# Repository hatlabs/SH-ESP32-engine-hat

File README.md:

# Engine Top Hat for SH-ESP32

This repository contains the hardware design files for the Engine Top Hat for SH-ESP32 (Engine Hat for short).

Engine Hat is a add-on circuit board that provides useful circuitry for connecting tachometers (RPM sensors), tank level sensors and engine alarms to an [SH-ESP32](https://hatlabs.github.io/sh-esp32).

The SH-ESP32 Engine Hat will be eventually available for purchase at [hatlabs.fi](https://hatlabs.fi).

Top view:

Bottom view:

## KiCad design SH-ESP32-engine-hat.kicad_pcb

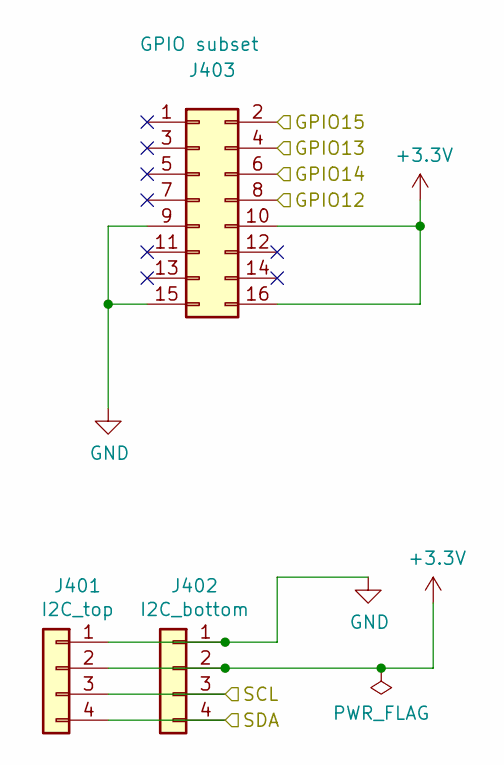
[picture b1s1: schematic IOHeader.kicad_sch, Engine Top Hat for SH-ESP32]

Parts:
J401: I2C_top; PinSocket_1x04_P2.54mm_Vertical; LCSC C225501
J402: I2C_bottom; PinHeader_1x04_P2.54mm_Vertical; LCSC C492403
J403: GPIO subset; PinSocket_2x08_P2.54mm_Vertical; LCSC C30734

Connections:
/Analog input/SCL: J401.3, J402.3; also elsewhere on the board
/Analog input/SDA: J401.4, J402.4; also elsewhere on the board
/DI1: J403.2; also elsewhere on the board
/DI2: J403.4; also elsewhere on the board
/DI3: J403.6; also elsewhere on the board
/DI4: J403.8; also elsewhere on the board
GND: J401.1, J402.1, J403.9, J403.15; also elsewhere on the board

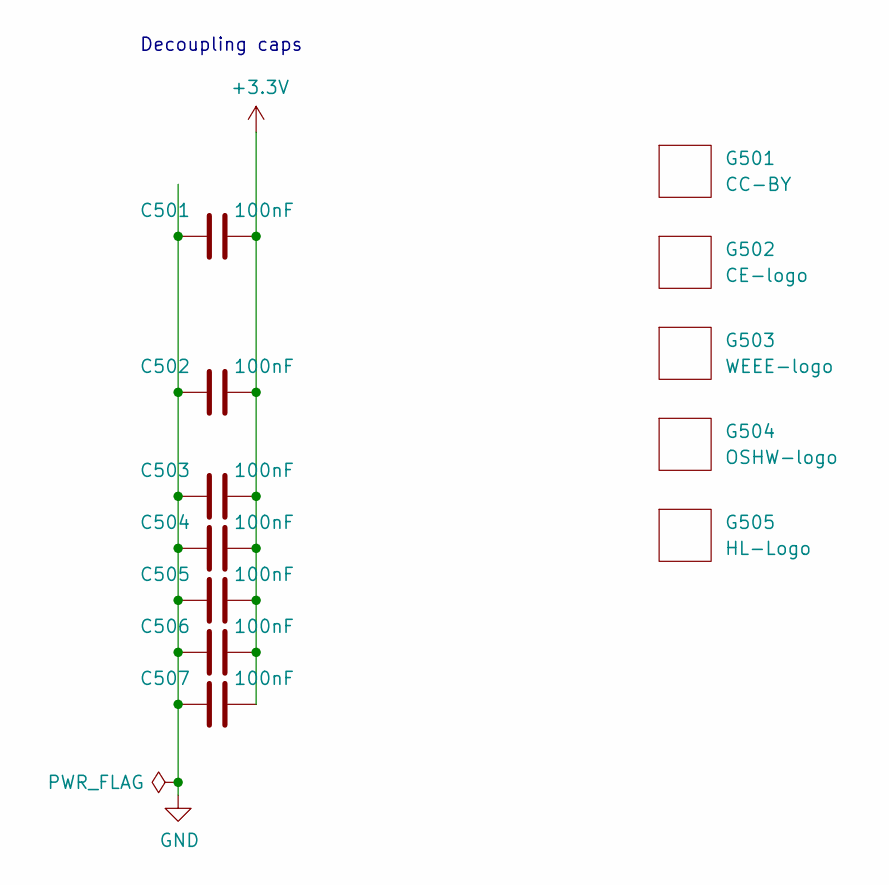
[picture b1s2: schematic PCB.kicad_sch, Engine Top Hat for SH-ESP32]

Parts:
C501, C502, C503, C504, C505, C506, C507: 100nF; C_0402_1005Metric; LCSC C1525
G501: CC-BY; cc-by_5mm
G502: CE-logo; CE-Logo_11.2x8mm_SilkScreen
G503: WEEE-logo; WEEE-Logo_5.6x8mm_SilkScreen
G504: OSHW-logo; OSHW-Logo2_9.8x8mm_SilkScreen
G505: HL-Logo; Hat_Labs_20mm

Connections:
GND: C501.1, C502.1, C503.1, C504.1, C505.1, C506.1, C507.1; also elsewhere on the board

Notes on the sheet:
Decoupling caps

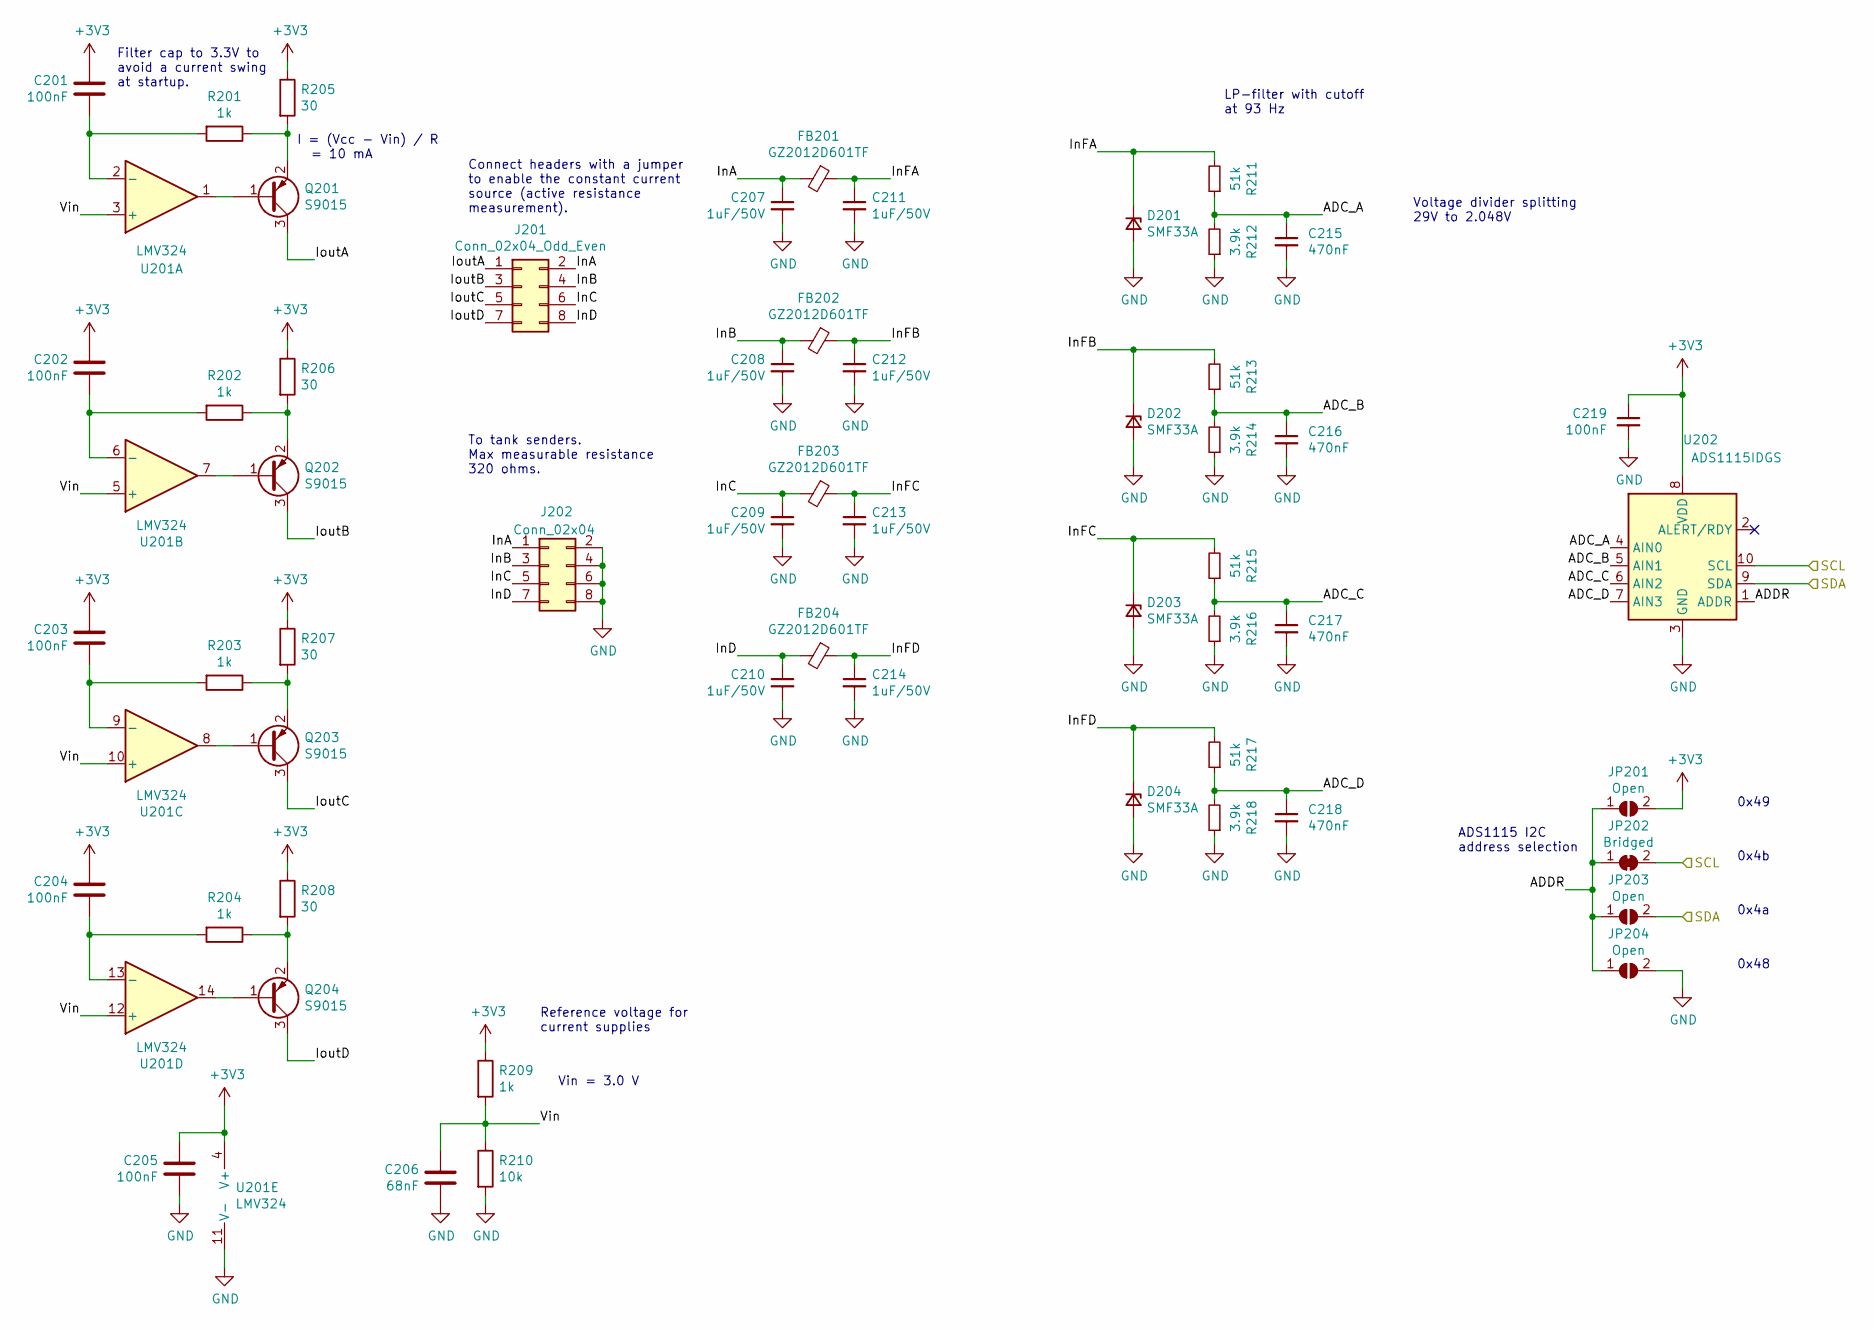
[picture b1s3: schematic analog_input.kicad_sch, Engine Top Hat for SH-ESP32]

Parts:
C201, C202, C203, C204, C205, C219: 100nF; C_0402_1005Metric; LCSC C1525
C206: 68nF; C_0603_1608Metric; LCSC C31658
C207, C208, C209, C210, C211, C212, C213, C214: 1uF/50V; C_0603_1608Metric; LCSC C15849
C215, C216, C217, C218: 470nF; C_0402_1005Metric; LCSC C47339
D201, D202, D203, D204: SMF33A; D_SOD-123F; LCSC C523840
FB201, FB202, FB203, FB204: GZ2012D601TF; L_0805_2012Metric; LCSC C1017
J201: Conn_02x04_Odd_Even; PinHeader_2x04_P2.54mm_Vertical; LCSC C124386
J202: Conn_02x04; PinHeader_2x04_P2.54mm_Horizontal; LCSC C358706
JP201, JP203, JP204: Open; SolderJumper-2_P1.3mm_Open_Pad1.0x1.5mm
JP202: Bridged; SolderJumper-2_P1.3mm_Bridged2Bar_RoundedPad1.0x1.5mm
Q201, Q202, Q203, Q204: S9015; SOT-323_SC-70; LCSC C106811
R201, R202, R203, R204, R209: 1k; R_0402_1005Metric; LCSC C11702
R205, R206, R207, R208: 30; R_0603_1608Metric; LCSC C22985
R210: 10k; R_0402_1005Metric; LCSC C25744
R211, R213, R215, R217: 51k; R_0402_1005Metric; LCSC C25794
R212, R214, R216, R218: 3.9k; R_0402_1005Metric; LCSC C51721
U201: LMV324; SOIC-14_3.9x8.7mm_P1.27mm; LCSC C362275
U202: ADS1115IDGS; TSSOP-10_3x3mm_P0.5mm; LCSC C37593

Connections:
/Analog input/ADC_A: C215.1, R211.1, R212.2, U202.4 (AIN0)
/Analog input/ADC_B: C216.1, R213.1, R214.2, U202.5 (AIN1)
/Analog input/ADC_C: C217.1, R215.1, R216.2, U202.6 (AIN2)
/Analog input/ADC_D: C218.1, R217.1, R218.2, U202.7 (AIN3)
/Analog input/ADDR: JP201.1 (A), JP202.1 (A), JP203.1 (A), JP204.1 (A), U202.1 (ADDR)
/Analog input/InA: C207.1, FB201.2, J201.2, J202.1
/Analog input/InB: C208.1, FB202.2, J201.4, J202.3
/Analog input/InC: C209.1, FB203.2, J201.6, J202.5
/Analog input/InD: C210.1, FB204.2, J201.8, J202.7
/Analog input/InFA: C211.1, D201.1 (K), FB201.1, R211.2
/Analog input/InFB: C212.1, D202.1 (K), FB202.1, R213.2
/Analog input/InFC: C213.1, D203.1 (K), FB203.1, R215.2
/Analog input/InFD: C214.1, D204.1 (K), FB204.1, R217.2
/Analog input/IoutA: J201.1, Q201.3 (C)
/Analog input/IoutB: J201.3, Q202.3 (C)
/Analog input/IoutC: J201.5, Q203.3 (C)
/Analog input/IoutD: J201.7, Q204.3 (C)
/Analog input/SCL: JP202.2 (B), U202.10 (SCL); also elsewhere on the board
/Analog input/SDA: JP203.2 (B), U202.9 (SDA); also elsewhere on the board
/Analog input/Vin: C206.1, R209.2, R210.1, U201.3 (+), U201.5 (+), U201.10 (+), U201.12 (+)
GND: C205.2, C206.2, C207.2, C208.2, C209.2, C210.2, C211.2, C212.2, C213.2, C214.2, C215.2, C216.2, C217.2, C218.2, C219.2, D201.2 (A), D202.2 (A), D203.2 (A), D204.2 (A), J202.2, J202.4, J202.6, J202.8, JP204.2 (B), R210.2, R212.1, R214.1, R216.1, R218.1, U201.11 (V-), U202.3 (GND); also elsewhere on the board
unnamed: C201.1, R201.2, U201.2 (-)
unnamed: C202.1, R202.2, U201.6 (-)
unnamed: C203.1, R203.2, U201.9 (-)
unnamed: C204.1, R204.2, U201.13 (-)
unnamed: Q201.1 (B), U201.1
unnamed: Q201.2 (E), R201.1, R205.2
unnamed: Q202.1 (B), U201.7
unnamed: Q202.2 (E), R202.1, R206.2
unnamed: Q203.1 (B), U201.8
unnamed: Q203.2 (E), R203.1, R207.2
unnamed: Q204.1 (B), U201.14
unnamed: Q204.2 (E), R204.1, R208.2

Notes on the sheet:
Vin = 3.0 V
ADS1115 I2C address selection
0x49
I = (Vcc - Vin) / R = 10 mA
Voltage divider splitting 29V to 2.048V
0x48
To tank senders. Max measurable resistance 320 ohms.
0x4a
Reference voltage for current supplies
0x4b
LP-filter with cutoff at 93 Hz
Connect headers with a jumper to enable the constant current source (active resistance measurement).
Filter cap to 3.3V to avoid a current swing at startup.

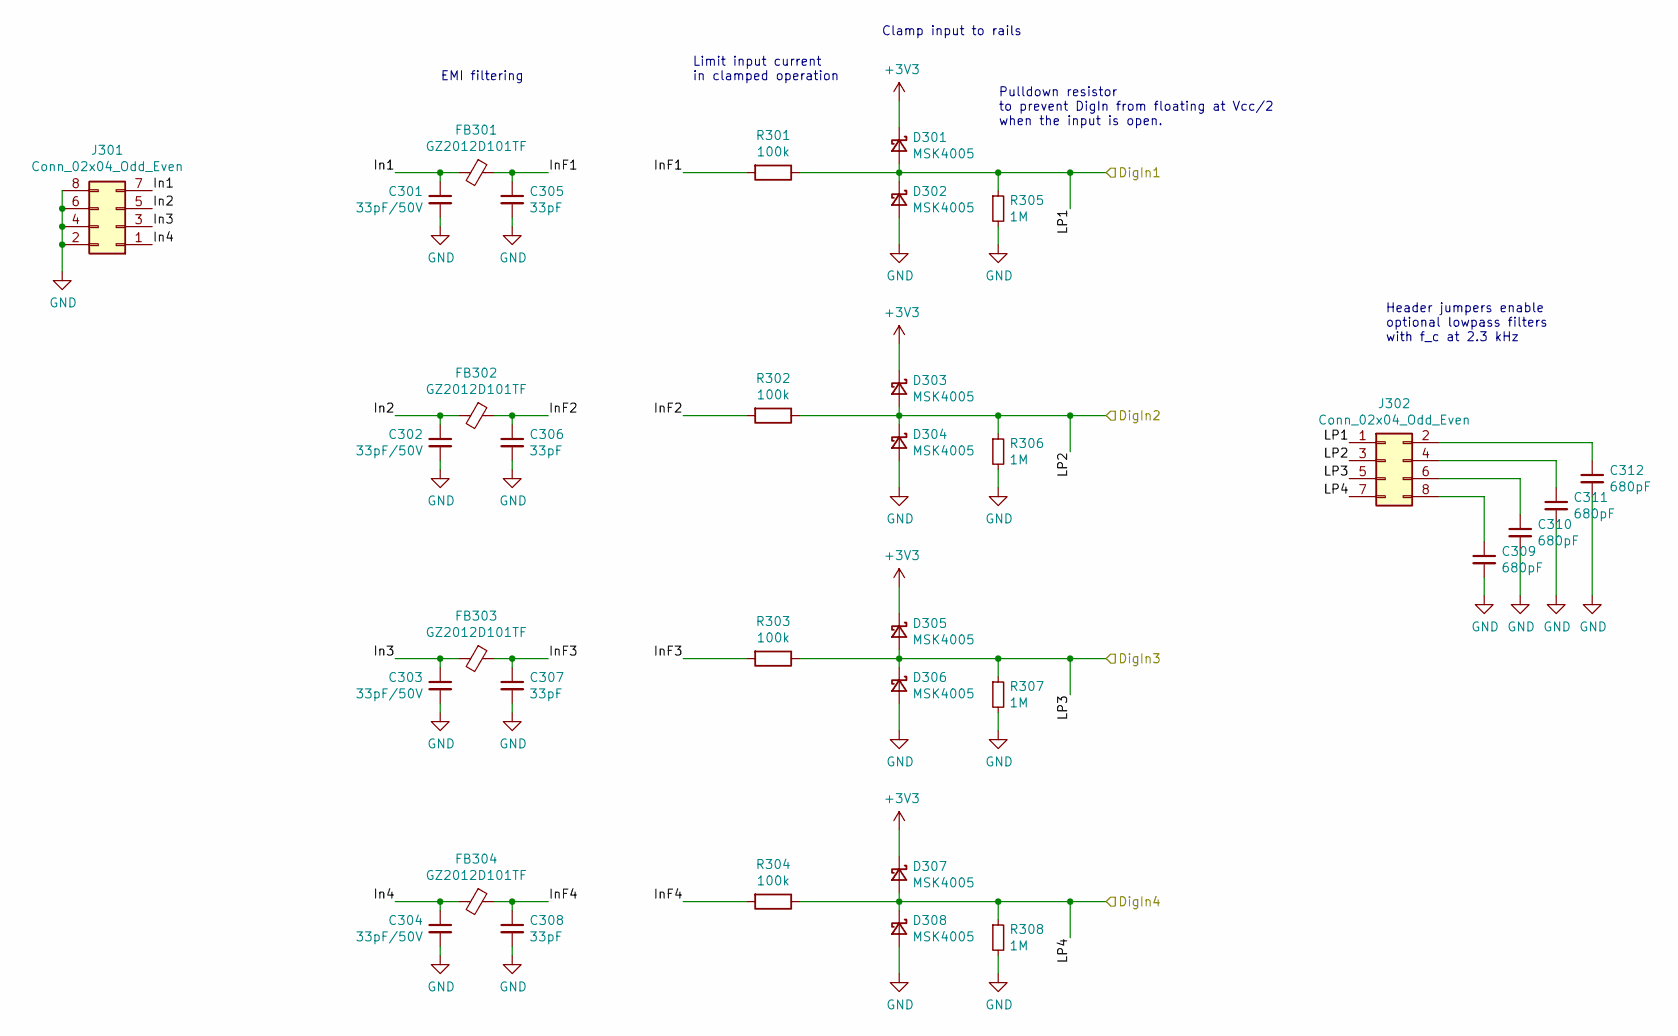
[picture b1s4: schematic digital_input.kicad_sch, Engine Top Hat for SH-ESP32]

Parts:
C301, C302, C303, C304: 33pF/50V; C_0603_1608Metric; LCSC C1663
C305, C306, C307, C308: 33pF; C_0402_1005Metric; LCSC C1562
C309, C310, C311, C312: 680pF; C_0603_1608Metric; LCSC C1630
D301, D302, D303, D304, D305, D306, D307, D308: MSK4005; D_SOD-523; LCSC C345957
FB301, FB302, FB303, FB304: GZ2012D101TF; L_0805_2012Metric; LCSC C1015
J301: Conn_02x04_Odd_Even; PinHeader_2x04_P2.54mm_Horizontal; LCSC C358706
J302: Conn_02x04_Odd_Even; PinHeader_2x04_P2.54mm_Vertical; LCSC C124386
R301, R302, R303, R304: 100k; R_0402_1005Metric; LCSC C25741
R305, R306, R307, R308: 1M; R_0402_1005Metric; LCSC C26083

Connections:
/DI1: D301.2 (A), D302.1 (K), J302.1, R301.1, R305.1; also elsewhere on the board
/DI2: D303.2 (A), D304.1 (K), J302.3, R302.1, R306.1; also elsewhere on the board
/DI3: D305.2 (A), D306.1 (K), J302.5, R303.1, R307.1; also elsewhere on the board
/DI4: D307.2 (A), D308.1 (K), J302.7, R304.1, R308.1; also elsewhere on the board
/Digital input/In1: C301.1, FB301.2, J301.7
/Digital input/In2: C302.1, FB302.2, J301.5
/Digital input/In3: C303.1, FB303.2, J301.3
/Digital input/In4: C304.1, FB304.2, J301.1
/Digital input/InF1: C305.1, FB301.1, R301.2
/Digital input/InF2: C306.1, FB302.1, R302.2
/Digital input/InF3: C307.1, FB303.1, R303.2
/Digital input/InF4: C308.1, FB304.1, R304.2
GND: C301.2, C302.2, C303.2, C304.2, C305.2, C306.2, C307.2, C308.2, C309.2, C310.2, C311.2, C312.2, D302.2 (A), D304.2 (A), D306.2 (A), D308.2 (A), J301.2, J301.4, J301.6, J301.8, R305.2, R306.2, R307.2, R308.2; also elsewhere on the board
unnamed: C309.1, J302.8
unnamed: C310.1, J302.6
unnamed: C311.1, J302.4
unnamed: C312.1, J302.2

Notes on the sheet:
Pulldown resistor to prevent DigIn from floating at Vcc/2 when the input is open.
EMI filtering
Clamp input to rails
Header jumpers enable optional lowpass filters with f_c at 2.3 kHz
Limit input current in clamped operation

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
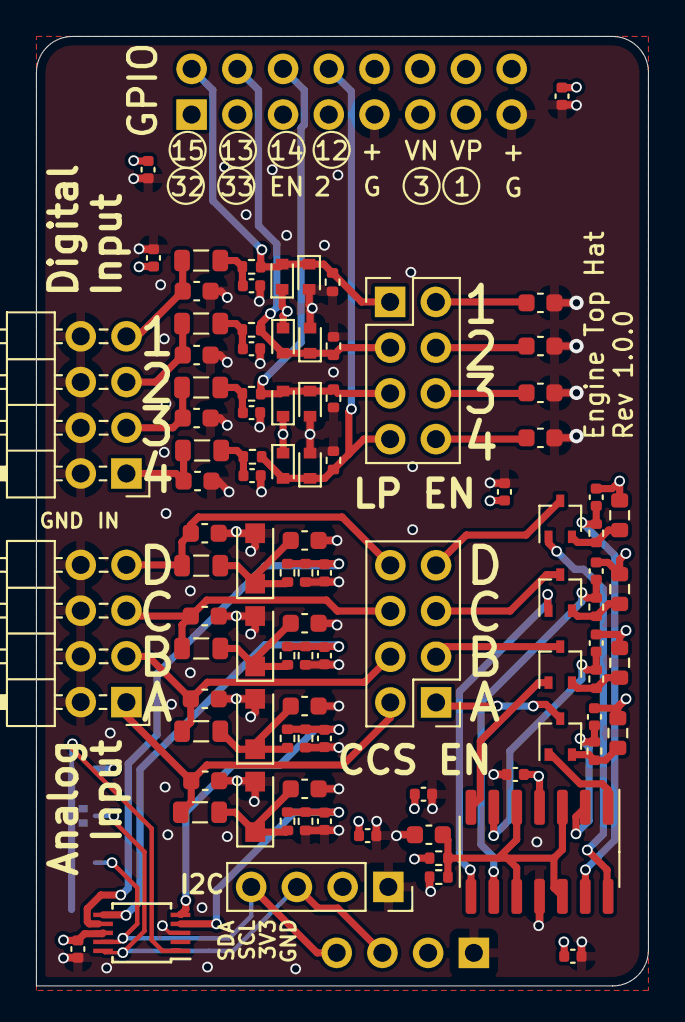
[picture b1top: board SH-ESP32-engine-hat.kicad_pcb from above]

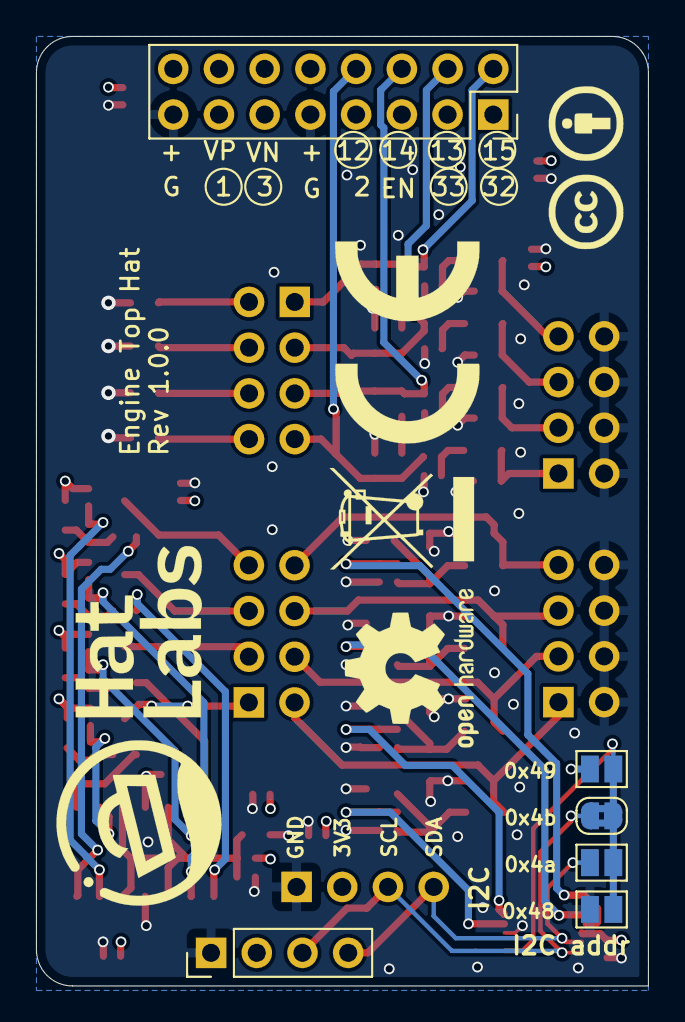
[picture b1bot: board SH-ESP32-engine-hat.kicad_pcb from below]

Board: 4 copper layers, 34.0 x 52.8 mm, 106 parts (11 on the bottom side), 50 nets.

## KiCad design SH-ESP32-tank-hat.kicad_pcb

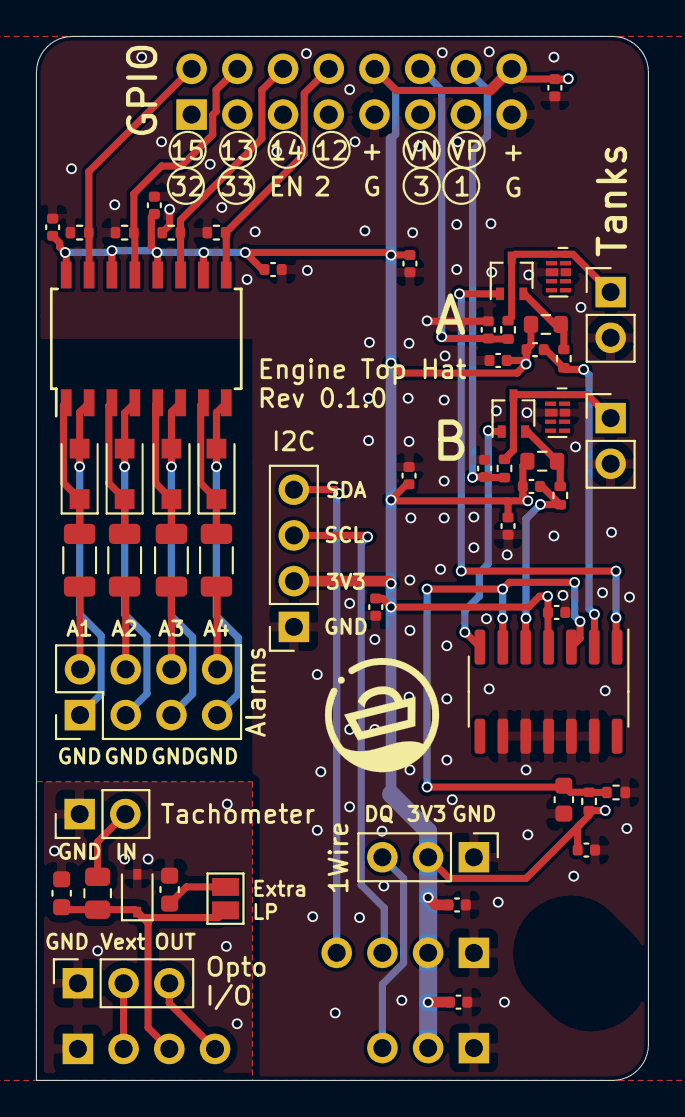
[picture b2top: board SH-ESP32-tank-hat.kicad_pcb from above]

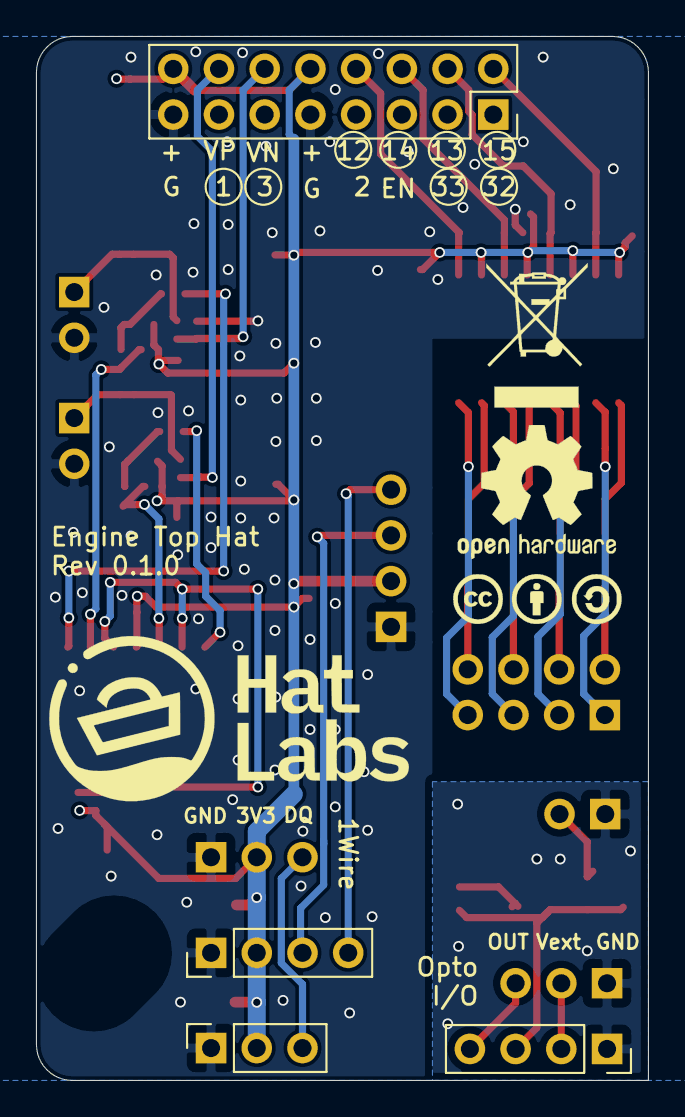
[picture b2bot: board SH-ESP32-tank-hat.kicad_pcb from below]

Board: 2 copper layers, 34.0 x 58.0 mm, 61 parts (4 on the bottom side), 38 nets.

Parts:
C201, C202, C203, C204, C205, C206, C207, C208, C209, C210, C211, C212, C401, C402, C403: 100nF; C_0402_1005Metric
C404: 68nF; C_0603_1608Metric
C405, C406: 1uF; C_0402_1005Metric
C501: 47nF; C_0603_1608Metric
C502: 4.7nF; C_0603_1608Metric
D501: BZT52C16S; D_SOD-323
D601, D602, D603, D604: SM4007PL; D_SOD-123F
H202: MountingHole; MountingSlot_3.2mm_M3_Unplated
J301: I2C_top; PinSocket_1x04_P2.54mm_Vertical
J302: I2C_bottom; PinHeader_1x04_P2.54mm_Vertical
J303: GPIO subset; PinSocket_2x08_P2.54mm_Vertical
J304: Opto_bottom; PinSocket_1x04_P2.54mm_Vertical
J305: 1-Wire_top; PinHeader_1x03_P2.54mm_Vertical
J306: 1-Wire_bottom; PinSocket_1x03_P2.54mm_Vertical
J307: Opto_top; PinSocket_1x03_P2.54mm_Vertical
J401, J402, J501: Conn_01x02; PinHeader_1x02_P2.54mm_Vertical
J601: Alarm input; PinHeader_2x04_P2.54mm_Vertical
JP501: SolderJumper_2_Open; SolderJumper-2_P1.3mm_Open_Pad1.0x1.5mm
Q401, Q402: S9015; SOT-323_SC-70
R401, R402, R405: 1k; R_0402_1005Metric
R403, R404: 30; R_0603_1608Metric
R406: 10k; R_0402_1005Metric
R407, R408: 1.5k; R_0402_1005Metric
R501: 3.3k; R_0805_2012Metric
R601, R602, R603, R604: 3.3k; R_1206_3216Metric
R605, R606, R607, R608: 2.2k; R_0402_1005Metric
U401: LMV324; SOIC-14_3.9x8.7mm_P1.27mm
U402, U403: RCLAMP0524P-N; Diodes_UDFN-10_1.0x2.5mm_P0.5mm
U601: ELQ3H7; SOIC-16W_5.3x10.2mm_P1.27mm

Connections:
+3V3: C201.2, C202.2, C203.2, C204.2, C205.2, C206.2, C207.2, C208.2, C209.2, C210.2, C211.2, C212.2, C401.2, C402.2, C403.1, J301.2, J302.2, J303.10, J303.16, J305.2, J306.2, R403.1, R404.1, R405.1, U401.4, U601.10, U601.12, U601.14, U601.16
/AL1: J303.2, R605.1, U601.15
/AL2: J303.4, R606.1, U601.13
/AL3: J303.6, R607.1, U601.11
/AL4: J303.8, R608.1, U601.9
/IOHeader/DQ: J305.3, J306.3
/IOHeader/ISO_OUT: J304.4, J307.3
/IOHeader/SCL: J301.3, J302.3
/IOHeader/SDA: J301.4, J302.4
/IOHeader/V_ISO: J304.2, J307.2
/ISO_IN: C502.1, D501.1, J304.3, JP501.2, R501.1
/Optocoupler input/GND1: D601.2, J601.1, U601.2
/Optocoupler input/GND2: D602.2, J601.3, U601.4
/Optocoupler input/GND3: D603.2, J601.5, U601.6
/Optocoupler input/GND4: D604.2, J601.7, U601.8
/Optocoupler input/IN1: J601.2, R601.1
/Optocoupler input/IN2: J601.4, R602.1
/Optocoupler input/IN3: J601.6, R603.1
/Optocoupler input/IN4: J601.8, R604.1
/Tank sender/ADC_A: C405.1, J303.12, R407.1
/Tank sender/ADC_B: C406.1, J303.14, R408.1
/Tank sender/Vin: C404.1, R405.2, R406.1, U401.3, U401.6
/Tank sender/VoutA: J401.1, Q401.3, R407.2, U402.1, U402.10
/Tank sender/VoutB: J402.1, Q402.3, R408.2, U403.1, U403.10
GND: C201.1, C202.1, C203.1, C204.1, C205.1, C206.1, C207.1, C208.1, C209.1, C210.1, C211.1, C212.1, C403.2, C404.2, C405.2, C406.2, J301.1, J302.1, J303.9, J303.15, J305.1, J306.1, J401.2, J402.2, R406.2, R605.2, R606.2, R607.2, R608.2, U401.9, U401.10, U401.11, U401.12, U401.13, U402.3, U402.8, U403.3, U403.8
ISO_GND: C501.2, C502.2, D501.2, J304.1, J307.1, J501.1
unnamed: C401.1, R401.2, U401.2
unnamed: C402.1, R402.2, U401.5
unnamed: C501.1, JP501.1
unnamed: D601.1, R601.2, U601.1
unnamed: D602.1, R602.2, U601.3
unnamed: D603.1, R603.2, U601.5
unnamed: D604.1, R604.2, U601.7
unnamed: J501.2, R501.2
unnamed: Q401.1, U401.1
unnamed: Q401.2, R401.1, R403.2
unnamed: Q402.1, U401.7
unnamed: Q402.2, R402.1, R404.2

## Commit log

2021-04-06 initial import
2021-04-21 Add a .gitignore file
2021-04-21 Create schema for tank and RPM sensors
2021-04-22 Initial PCB layout
2021-04-23 Reduce the PCB size; switch to TLA2024
2021-04-23 New design with only two channels and using ESP32 internal ADCs
2021-04-27 Add 4x optocoupler input for alarms and other use
2021-04-27 Update document metadata
2021-04-27 Rename tank-hat to engine-hat
2021-04-27 Make all TH headers virtual
2021-04-27 Fix the footprint for ELQ3H7
2021-04-27 Add README
2021-04-27 Change opto top conx from a socket to a header
2021-04-28 Fix the wrong LCSC component for R501
    Also silkscreen fixes
2021-05-20 Fix the reversed tank input B opto inputs
2021-07-03 Redesign with unisolated inputs
2021-08-16 Change DIP switches to headers
2021-08-16 Change license to CC-BY.
2021-08-16 Routing fixes
2021-08-17 Add solder pads for I2C address selection
    Also pre-emptive CE mark
2021-12-31 Fix JLCPCB tooling hole footprint
2021-12-31 Bump version number
2021-12-31 Save in KiCad 6 format
2021-12-31 Fix DRC errors
2021-12-31 Bump the version number
2021-12-31 Remove tooling holes
2021-12-31 Crop the copper zones to PCB area
2022-02-02 Fix solder jumper silkscreen
2022-02-03 Add PCB graphics as symbols
2022-02-03 Add the KiKit footprint library
2022-02-03 Add panel tab annotations
2022-02-03 Refill zones, remove JLC order number template
2022-02-03 Replace C211-214 with 50V 0603 footprint parts
2022-02-03 Update sheet data; refill
2022-02-03 Add fab file creation scripts
2022-02-03 Update README images

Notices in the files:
IOHeader.kicad_sch:
https://creativecommons.org/licenses/by/4.0
This design is licensed under CC BY 4.0.
SH-ESP32-engine-hat.kicad_pcb:
https://creativecommons.org/licenses/by-sa/4.0
This design is licensed under CC BY-SA 4.0.
SH-ESP32-tank-hat.kicad_pcb:
Sailor Hat for ESP32 is licensed under CC BY-SA 4.0.
